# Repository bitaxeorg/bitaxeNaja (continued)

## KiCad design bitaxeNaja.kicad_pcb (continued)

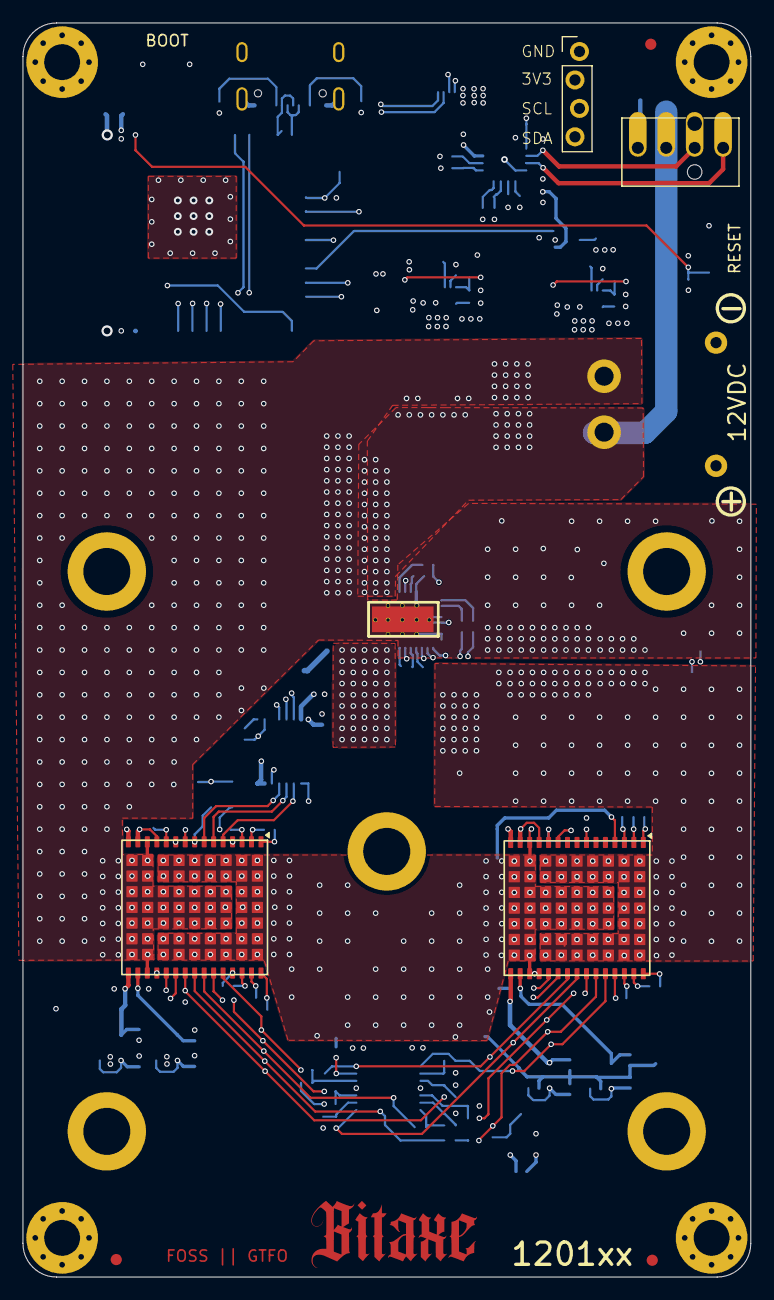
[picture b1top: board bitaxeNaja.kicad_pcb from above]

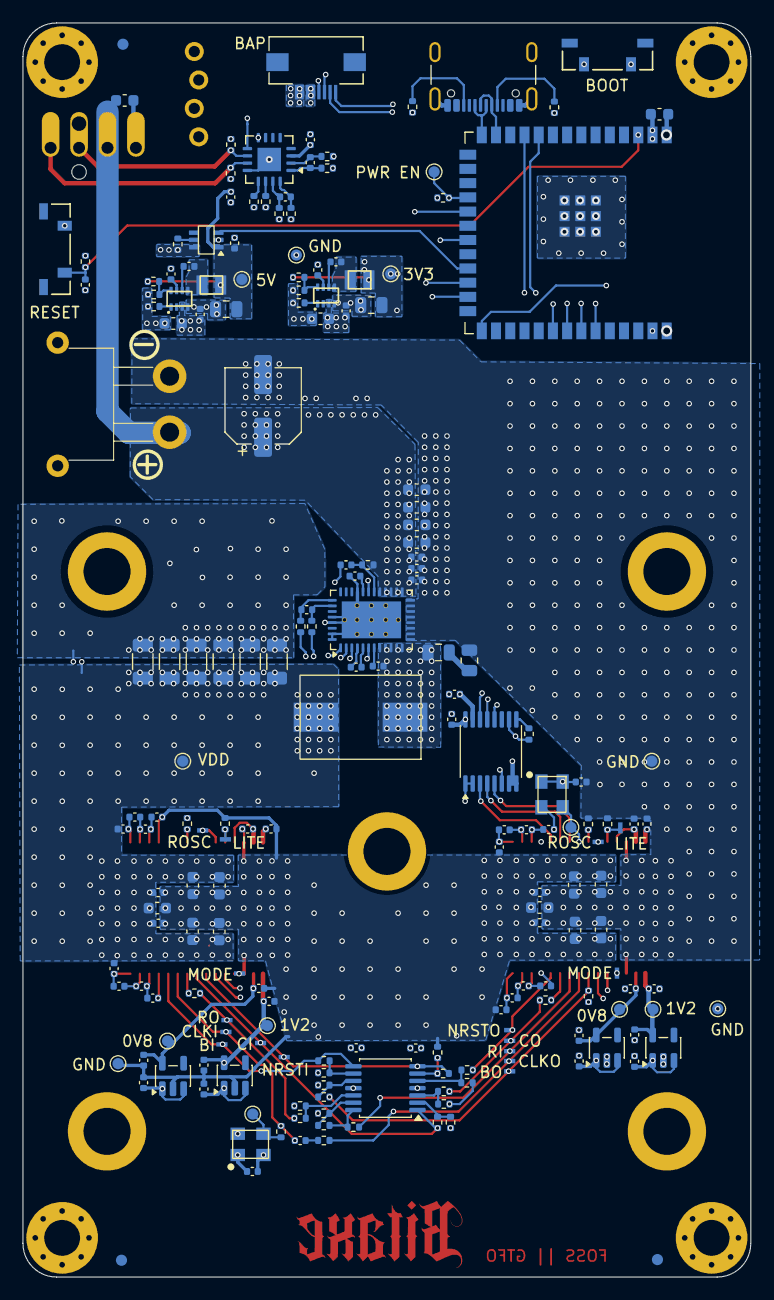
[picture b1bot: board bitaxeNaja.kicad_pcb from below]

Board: 6 copper layers, 65.0 x 112.0 mm, 209 parts (196 on the bottom side), 112 nets.

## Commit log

2025-07-17 initial import
2025-07-18 added BM1340 footprint
2025-07-18 updated power pads. added BM1370 pinout for BM1340 (??)
2025-07-19 lots of routing
2025-08-01 placed and routed and DRC'd. updated TPS546 for 1.0V output.
2025-08-01 added checked gerbers and BOM
2025-08-01 updated render and readme
2025-08-04 added webench design
2026-04-15 Ignore manufacturing files
2026-04-15 update to KiCad 10
2026-06-18 switched to single phase TPS546D24 and put the ASICs in series.
2026-06-24 rough parts placement.
2026-06-25 finished placing parts. lots of routing.
2026-06-25 add missing 3d models
2026-06-25 finished routing
2026-06-25 DRC pass
2026-06-26 make the PCB bigger for 70mm heatsink mounting holes
2026-06-28 AI BOM updates
2026-06-28 first pass DFM
2026-06-28 AGND and OSNS
2026-06-29 cleaned up kicad trailing whitespace warnings and normalized capacitor units
2026-06-29 Stop tracking KiCad history directory
2026-06-29 footprint, BOM cleanup. bypass capacitor spacing cleanup
2026-06-29 fix all DRC and ERC
2026-06-29 update readme and render
2026-06-29 moved the 3V3 level shifter down out of the main GND power plane. BOM cleanup
2026-06-29 power plane cleanup
2026-06-30 remove malformed fields in schematic
2026-06-30 bumped version to 1201xx. added fixes for #3
